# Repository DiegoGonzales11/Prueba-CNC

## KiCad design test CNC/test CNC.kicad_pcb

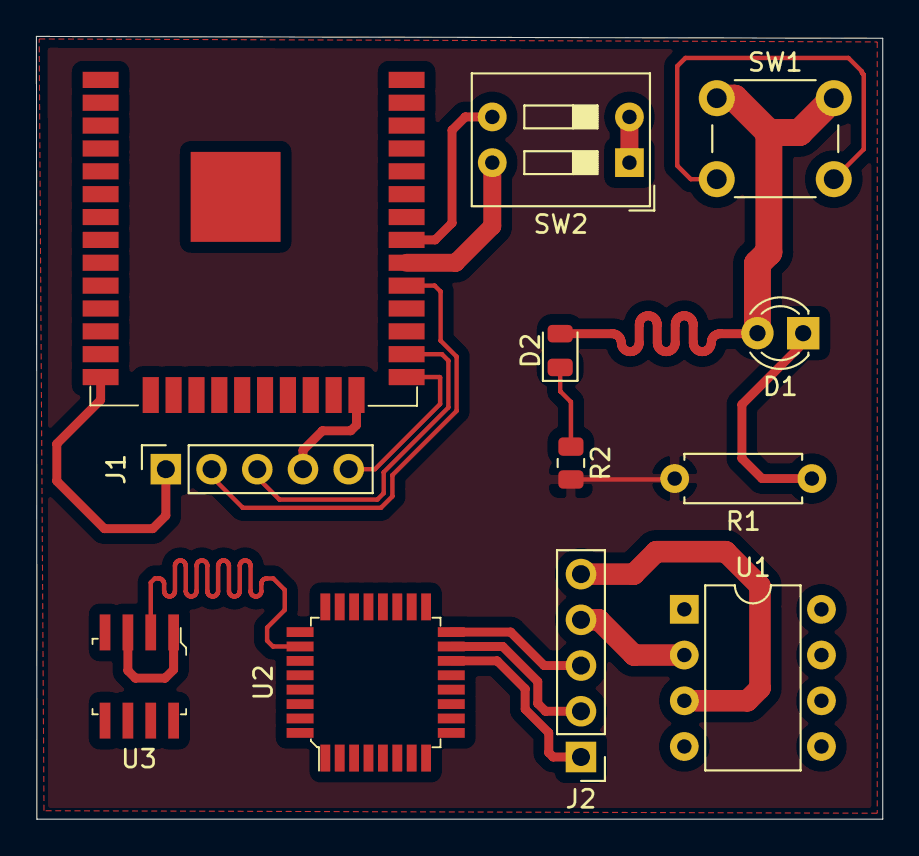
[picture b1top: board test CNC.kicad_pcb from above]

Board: 2 copper layers, 47.0 x 43.5 mm, 12 parts (0 on the bottom side), 19 nets.

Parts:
D1: LED; LED_D3.0mm
D2: LED; LED_0805_2012Metric
J1: Conn_01x05_Female; PinSocket_1x05_P2.54mm_Vertical
J2: Conn_01x05_Male; PinHeader_1x05_P2.54mm_Vertical
MOD1: ESP32-WROOM-32; ESP32-WROOM-32D
R1: R; R_Axial_DIN0207_L6.3mm_D2.5mm_P7.62mm_Horizontal
R2: R; R_0805_2012Metric
SW1: SW_MEC_5E; SW_PUSH_6mm_H8.5mm
SW2: SW_DIP_x02; SW_DIP_SPSTx02_Slide_9.78x7.26mm_W7.62mm_P2.54mm
U1: DS1302+; DIP-8_W7.62mm
U2: ATMEGA328-AU; TQFP-32_7x7mm
U3: LM393; SOIC-8_W3.9mm

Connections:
GND: R1.2, R2.2
unnamed: D1.1, R1.1
unnamed: D1.2, D2.2, SW1.1
unnamed: D2.1, R2.1
unnamed: J1.1, MOD1.14
unnamed: J1.2, MOD1.29
unnamed: J1.3, MOD1.26
unnamed: J1.4, MOD1.24
unnamed: J1.5, MOD1.25
unnamed: J2.1, U2.14
unnamed: J2.2, U2.15
unnamed: J2.3, U2.16
unnamed: J2.4, U1.2
unnamed: J2.5, U1.3
unnamed: MOD1.30, SW2.4
unnamed: MOD1.31, SW2.3
unnamed: U2.26, U3.2
unnamed: U3.1, U3.3
VCC: SW2.1, SW2.2

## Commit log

2021-02-02 sdds
